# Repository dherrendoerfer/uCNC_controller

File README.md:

Copyright (C) 2014,2015,2016,2017 D.Herrendoerfer 

# uCNC_controller: A small Arduino CNC

uCNC_controller is a small CNC G-Code interpreting controller for educational or home projects.  
It supports small set of commands and can be configured to behave in several different ways.  
Included in the Extras directory are sample files to replicate a controller circuit board and  
3D files to build a small 3 axis CNC plotter.

### uCNC_controller:
It controls up to three stepper motors via the Arduino stepper library, as well as one servo, and  
two general purpose outputs. It is programmed for simplicity and readability more than for being  
a feature-complete g-code interpreter. It is intended to be a stepping stone for people intending  
to learn about machine control.

### The Extras:
Within the Extras directory there are tools, layout and schematic files, control firmwares to  
extend the basic use example of a simple plotter. Feel free to delve.

Please read the included **uCNC_controller/README.txt** file for more information.  
Please read the included **LICENSE** files and make sure you understand them before redistributing anything from this repo.

### More Information
The original source code of uCNC_controller was developed for this project in 2013  

Also, feel free to check out my [YouTube Channel](https://www.youtube.com/channel/UCe9XrOQuQR8SzbB_zRUIf0w "Dirk Herrendoerfers YouTube Channel")
all the source code and project files from the projects  
featured on the channel are hosted here.

### Ready to order PCBs for uCNC_Controller
The circuit boards for the uCNC projects are available for viewing at the EasyEDA online PCB design 
web site and can be ordered directly through JCLPCB from that site. 

The direct link to my project space on EasyEDA is [https://easyeda.com/dherrendoerfer](https://easyeda.com/dherrendoerfer "Dirk Herrendoerfers EasyEDA Projects")

## Notes
- The beta directory contains pre-release versions of the controller firmware.
- To build the uCNC_controller firmware the Arduino stepper library is required.
- The firmware requires a 5V Arduino board with at least 13 digital and 6 Analog I/O ports.  
- Recommended are 32k of flash memory.  
- Among the supported boards are: Arduino Uno, Arduino Nano, Arduino Mega 2560, and many more.
- This is work-in-progress. Check back frequently.

Donations:  
If you would like to make a donation to keep this project and others going you can do so at:  
https://www.paypal.me/dherrendoerfer  
This helps a lot !

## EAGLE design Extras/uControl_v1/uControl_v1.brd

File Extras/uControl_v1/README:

Included here is a prototype layout for a controller circuit.

The uControl board is different from the previous versions and 
requires a different firmware than the other versions.

Features are:
--------------
Support for 3 bipolar steppers using A4988 Polulu driver modules.
Support for 1 servo
Support for 8 input lines 6 bare, 2 as switch inputs
Support for 1 high load output (5A/PWM)
Support for breakout of serial and reset lines

uControl_v1.sch
----------------
  The layout schematic file

uControl_v1.brd
----------------
  The layout source file (just the layout)

uControl_v1.ps, uControl_v1.pdf
--------------------------------
  Exported layout formats of the above board

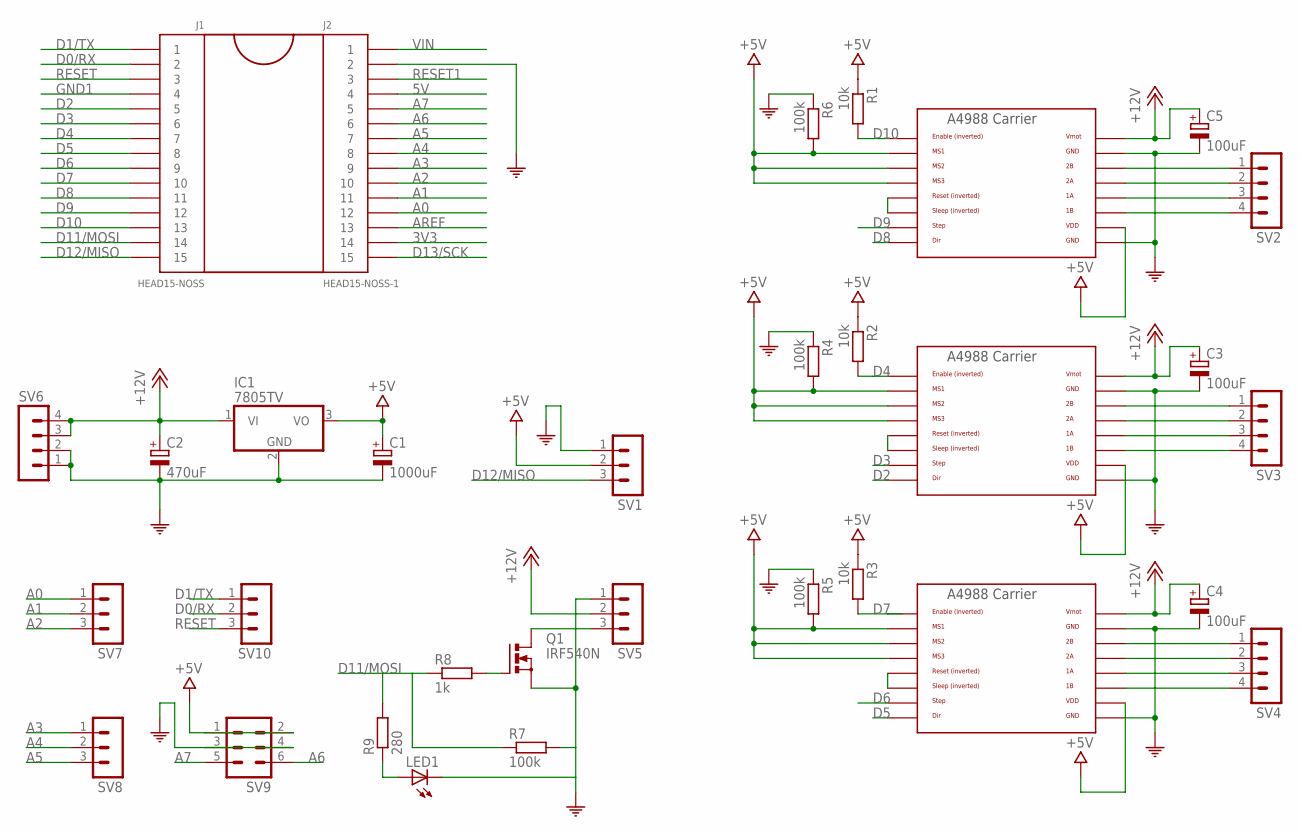
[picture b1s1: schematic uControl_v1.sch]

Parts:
C1: 1000uF; TAP5-70
C2: 470uF; TAP5-70
C3, C4, C5: 100uF; TAP5-70
IC1: 7805TV; TO220V
J1: HEAD15-NOSS
J2: HEAD15-NOSS-1
LED1: LED3MM
Q1: IRF540N; TO220BV
R1, R2, R3: 10k; 0207/10
R4, R5, R6, R7: 100k; 0207/10
R8: 1k; 0207/10
R9: 280; 0207/10
SV1, SV5, SV7, SV8, SV10: MA03-1
SV2, SV3, SV4, SV6: MA04-1
SV9: MA03-2
U$3: POLOLU_A4983CARRIER; A4988BREAKOUT
U$4, U$5: A4988BREAKOUT

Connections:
3V3: J2.14
5V: J2.4
+5V: C1.+, IC1.3 (VO), R1.1, R2.1, R3.1, R4.2, R5.2, R6.2, SV1.2, SV9.1, SV9.2, U$3.MS1, U$3.MS2, U$3.MS3, U$3.VDD, U$4.MS1, U$4.MS2, U$4.MS3, U$4.VDD, U$5.MS1, U$5.MS2, U$5.MS3, U$5.VDD
+12V: C2.+, C3.+, C4.+, C5.+, IC1.1 (VI), SV5.2, SV6.3, SV6.4, U$3.VMOT, U$4.VMOT, U$5.VMOT
A0: J2.12, SV7.1
A1: J2.11, SV7.2
A2: J2.10, SV7.3
A3: J2.9, SV8.1
A4: J2.8, SV8.2
A5: J2.7, SV8.3
A6: J2.6, SV9.6
A7: J2.5, SV9.5
AREF: J2.13
COM: C1.-, C2.-, C3.-, C4.-, C5.-, IC1.2 (GND), J2.2, LED1.K (C), Q1.S, R4.1, R5.1, R6.1, R7.2, SV1.1, SV5.1, SV6.1, SV6.2, SV9.3, SV9.4, U$3.GND, U$3.GND@0 (GND), U$4.GND, U$4.GND@0 (GND), U$5.GND, U$5.GND@0 (GND)
D0/RX: J1.2, SV10.2
D1/TX: J1.1, SV10.1
D2: J1.5, U$5.DIR
D3: J1.6, U$5.STEP
D4: J1.7, R2.2, U$5.EN
D5: J1.8, U$4.DIR
D6: J1.9, U$4.STEP
D7: J1.10, R3.2, U$4.EN
D8: J1.11, U$3.DIR
D9: J1.12, U$3.STEP
D10: J1.13, R1.2, U$3.EN
D11/MOSI: J1.14, R7.1, R8.1, R9.2
D12/MISO: J1.15, SV1.3
D13/SCK: J2.15
GND1: J1.4
unnamed: LED1.A, R9.1
unnamed: U$4.RST, U$4.SLP (SLEEP)
unnamed: SV2.1, U$3.2B
unnamed: U$3.RST, U$3.SLP (SLEEP)
unnamed: U$5.RST, U$5.SLP (SLEEP)
unnamed: SV2.2, U$3.2A
unnamed: SV2.3, U$3.1A
unnamed: SV2.4, U$3.1B
unnamed: SV3.1, U$5.2B
unnamed: SV3.2, U$5.2A
unnamed: SV3.3, U$5.1A
unnamed: SV3.4, U$5.1B
unnamed: SV4.1, U$4.2B
unnamed: SV4.2, U$4.2A
unnamed: SV4.3, U$4.1A
unnamed: SV4.4, U$4.1B
unnamed: Q1.D, SV5.3
unnamed: Q1.G, R8.2
RESET: J1.3, SV10.3
RESET1: J2.3
VIN: J2.1

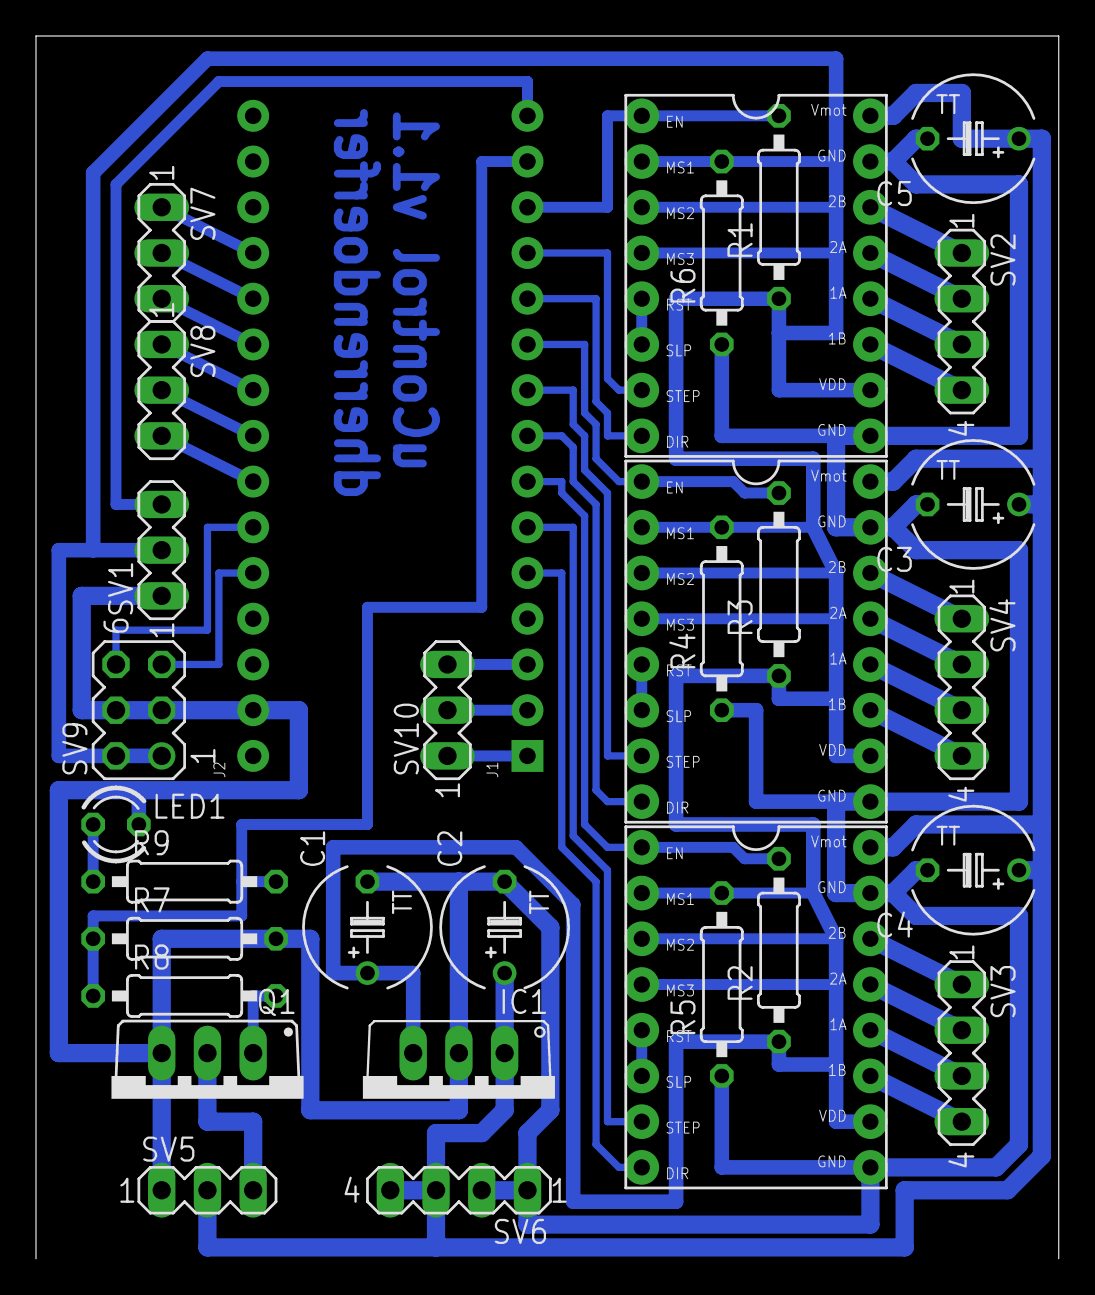
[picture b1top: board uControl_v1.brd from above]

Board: 2 copper layers, 56.8 x 67.9 mm, 32 parts (0 on the bottom side), 43 nets.

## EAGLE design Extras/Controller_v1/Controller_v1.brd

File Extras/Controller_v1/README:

Included here is a prototype layout for a controller circuit.
This controller circuit is identical to the Controller.brd 
with the exception that the Laser is driven with 12V, not 5V.

-- Beta warning: this has not jet been fully tested by me.

Controller_v1.brd
--------------
  The layout source file

Controller_v1.sch
--------------
  The schematic source file.

  Controller_v1.hpgl, Controller_v1.ps
--------------------------------------
  Exported layout formats of the above board

Controller_v1.hpgl.nc
---------------------
  A g-code sample file that will produce a plot of the above
  board using the included board and firmware.

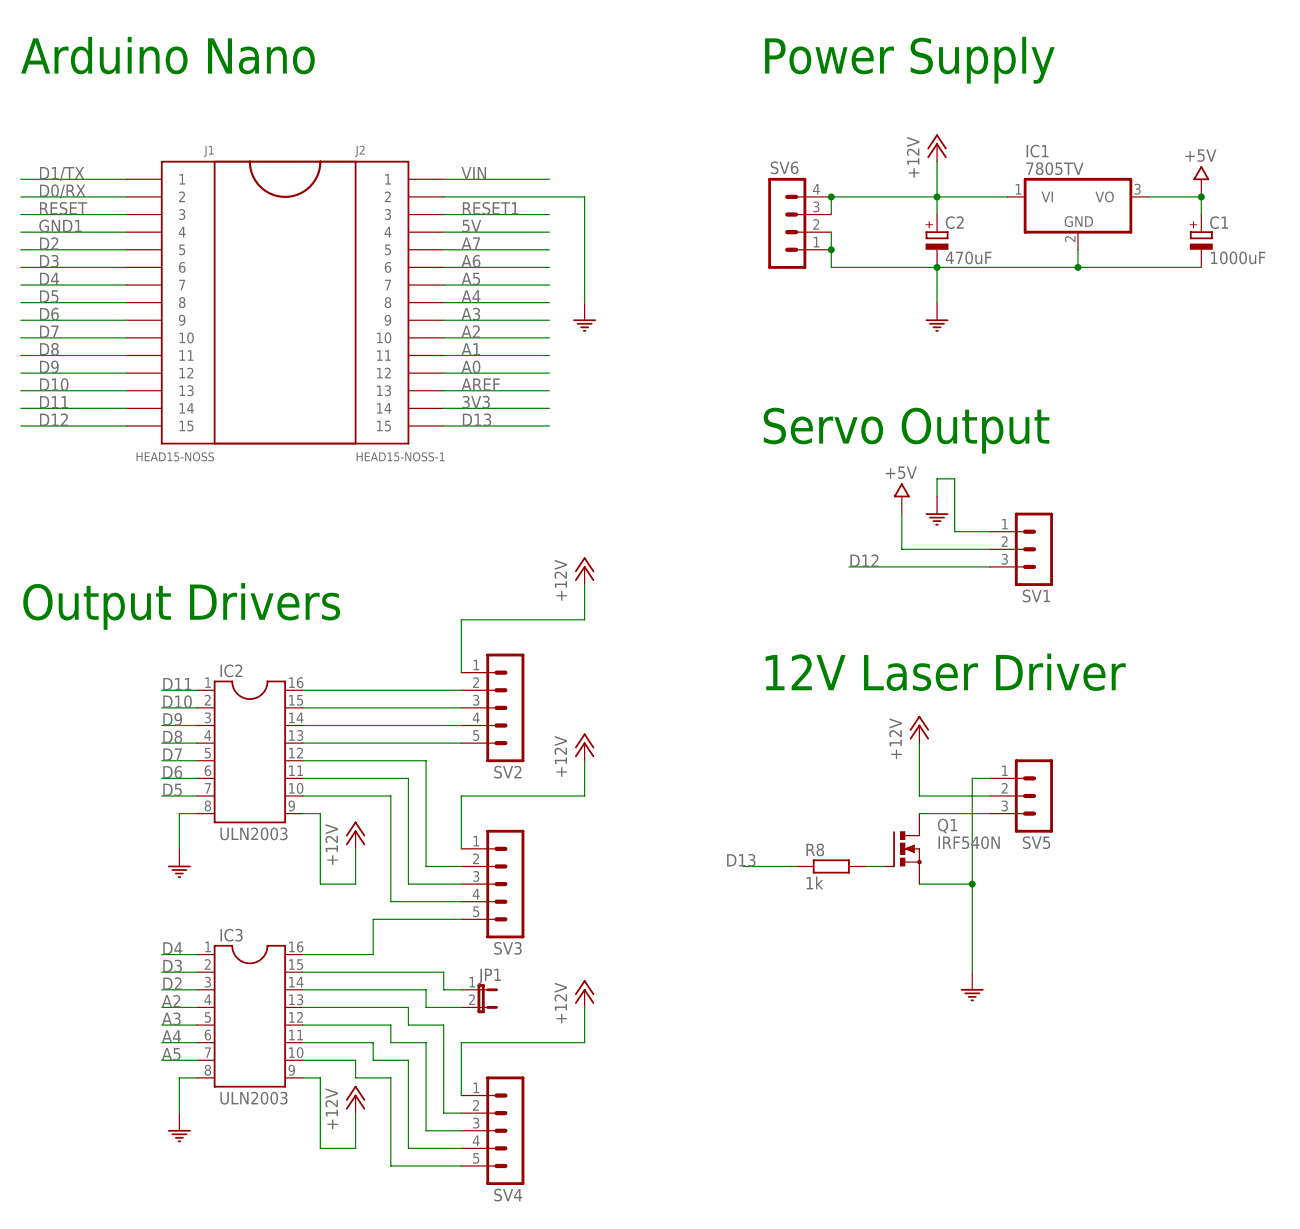
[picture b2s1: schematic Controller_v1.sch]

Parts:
C1: 1000uF; TAP5-70
C2: 470uF; TAP5-70
IC1: 7805TV; TO220V
IC2, IC3: ULN2003; DIL16
J1: HEAD15-NOSS
J2: HEAD15-NOSS-1
JP1: JP1E; JP1
Q1: IRF540N; TO220BV
R8: 1k; 0207/10
SV1, SV5: MA03-1
SV2, SV3, SV4: MA05-1
SV6: MA04-1

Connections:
3V3: J2.14
5V: J2.4
+5V: C1.+, IC1.3 (VO), SV1.2
+12V: C2.+, IC1.1 (VI), IC2.9, IC3.9, SV2.1, SV3.1, SV4.1, SV5.2, SV6.3, SV6.4
A0: J2.12
A1: J2.11
A2: IC3.4, J2.10
A3: IC3.5, J2.9
A4: IC3.6, J2.8
A5: IC3.7, J2.7
A6: J2.6
A7: J2.5
AREF: J2.13
COM: C1.-, C2.-, IC1.2 (GND), IC2.8, IC3.8, J2.2, Q1.S, SV1.1, SV5.1, SV6.1, SV6.2
D0/RX: J1.2
D1/TX: J1.1
D2: IC3.3, J1.5
D3: IC3.2, J1.6
D4: IC3.1, J1.7
D5: IC2.7, J1.8
D6: IC2.6, J1.9
D7: IC2.5, J1.10
D8: IC2.4, J1.11
D9: IC2.3, J1.12
D10: IC2.2, J1.13
D11: IC2.1, J1.14
D12: J1.15, SV1.3
D13: J2.15, R8.1
GND1: J1.4
unnamed: IC3.15, JP1.1
unnamed: IC3.14, JP1.2
unnamed: IC3.13, SV4.2
unnamed: IC3.12, SV4.3
unnamed: IC3.16, SV3.5
unnamed: IC3.11, SV4.4
unnamed: IC3.10, SV4.5
unnamed: Q1.D, SV5.3
unnamed: Q1.G, R8.2
unnamed: IC2.16, SV2.2
unnamed: IC2.15, SV2.3
unnamed: IC2.14, SV2.4
unnamed: IC2.13, SV2.5
unnamed: IC2.12, SV3.2
unnamed: IC2.11, SV3.3
unnamed: IC2.10, SV3.4
RESET: J1.3
RESET1: J2.3
VIN: J2.1

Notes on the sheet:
Arduino Nano
Output Drivers
Power Supply
Servo Output
12V Laser Driver

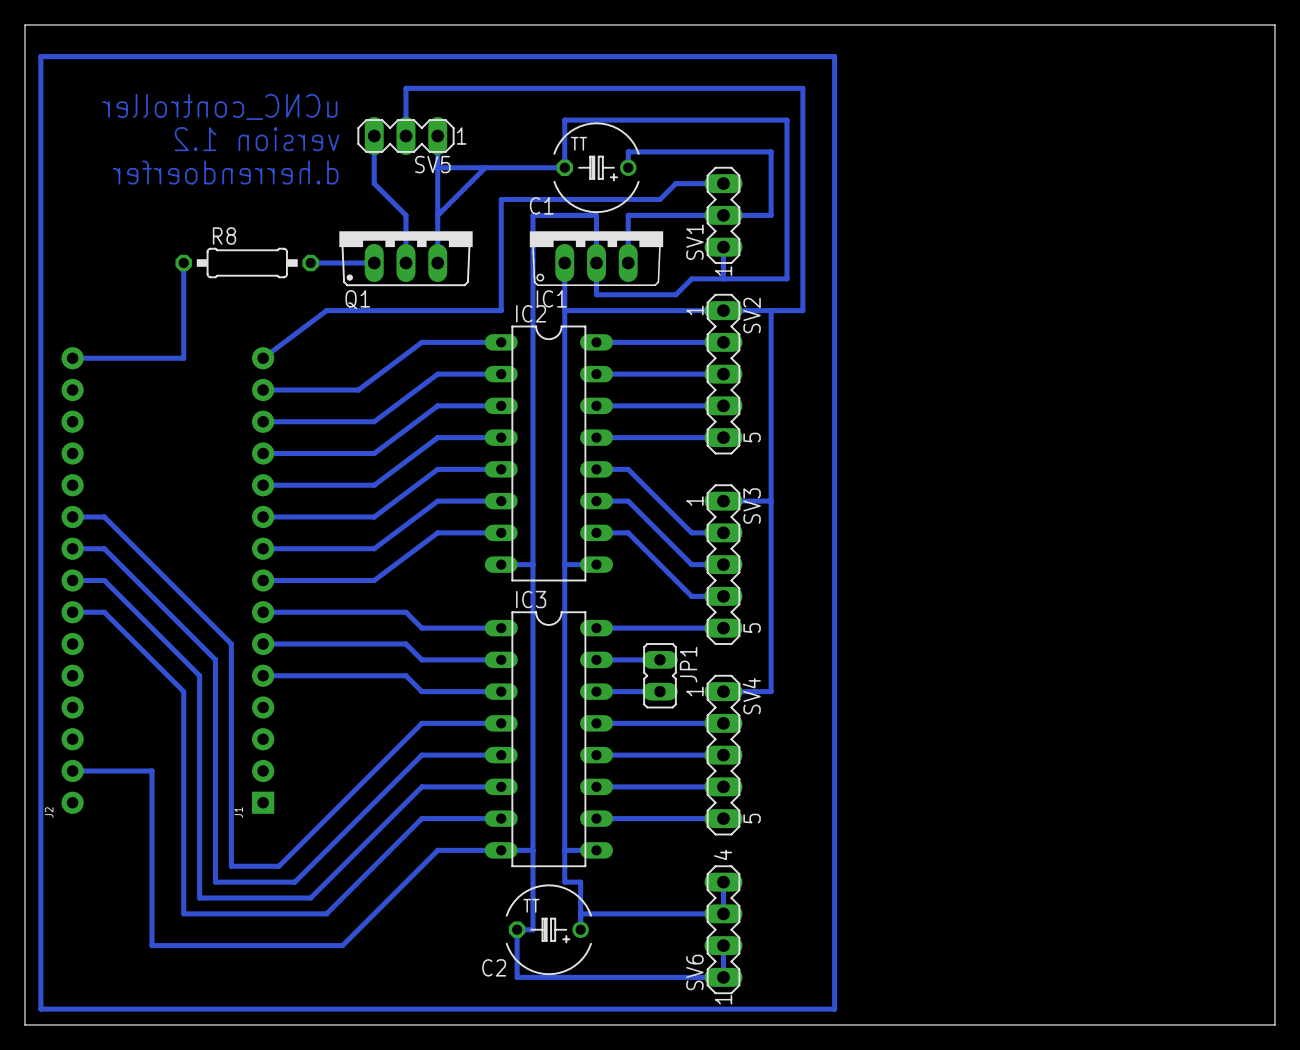
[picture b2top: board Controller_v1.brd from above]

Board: 2 copper layers, 100.0 x 80.0 mm, 16 parts (0 on the bottom side), 35 nets.

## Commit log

2014-02-09 Initial check-in.
2014-02-10 Updated documentation
2014-02-11 More documentation
2014-04-24 This commit adds the files needed to produce a small plotter that will work with this firmware. Included is the layout of a controller board and 3D files to print the required parts for the plotter i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
2014-04-24 Updated README file.
2014-07-14 Fix erroreous stepper speed setting in mode 1
2014-07-15 Add beta code for version 2
2014-07-15 Update beta version nummer
2014-07-17 Update beta readme file
2014-08-01 Update the stl files for the plotter to better work with slic3r.
2014-08-26 Update B.O.M.
2014-08-26 Update README file
2014-09-30 Add the files for the version 4 plotter, firmware, and controller.
2014-10-03 Add v4 beta code and reorganize directory structure
2014-10-07 Clean up to merge v1 and v4 controller codebase.
2014-11-18 Fix initializarion and position reset
2014-12-03 Organize the file and directory structure so sketches are easier to directly open in Arduino IDE if the git has been downloaded as a zip file (hopefully)
2014-12-28 Add schematic and board for the reworked v1 controller board.
2014-12-29 Add missing Controller_v1 files
2015-01-04 Add an ID string to the boot message
2015-01-08 Add GcodeWriter
2015-05-11 Fixed an initialization bug.
2015-05-27 Add Hp2xx Windows console application
2015-07-07 Added GRBL Polulu shield output layout
2015-07-08 Updates for GRBL-Shield support
2015-07-08 Add some cleanup and changes for the GRBL Shield. Also fix some minor issues with Z-Axis handling
2016-04-18 Fixed a nasty bug that would hit if the build area was bigger than 32k native steps.
2016-04-18 Fixed the same nasty 32k steps bug in the beta of the v1 firmware
2016-04-21 Fixed some typos, added more structure to the documentation, added copyright assignments to non-source files, as some forks and clones of this software have appeared that have the copyright assignmen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
2016-09-13 Update README for readability.
2016-09-14 Add new v6 beta code.
2016-12-27 Add v3 AllParts stl file
2016-12-31 Add v4 plotter files
2017-01-09 Update to documentation
2017-01-09 Documentation updates
2017-01-11 Circumvent timing issue
2017-01-11 Fix servo init timing issue
2017-01-12 Work to revive auto homing
2017-01-13 Back to conservative defaults for homing
2017-01-16 Small updates and license date changes, wip
2017-01-17 Push v6 beta to newest version, adding alpha servo support
2017-01-27 Introducing the engraver mode
2017-01-29 Add first beta of gcode4bmps.py
2017-02-01 Update readme, add test tux file.
2017-02-15 Add first set of parts to Rod-Robin CNC build
2017-03-15 Added documentation into the output file and raised pdf output dpi to 600
2017-05-25 Adding new code from recent projects
2017-08-25 Clean up documentation and fix a small issue in gcode4bmps
2017-08-25 Fix error in Z depth setting
2017-09-05 Add new functions for DPI handling and a cutout helper
2017-09-23 Add simple engraver support with spindle-on/off semantics
2017-10-09 Introduce V1_COMPACT board definition
2017-11-02 Add the LED-HMD code
2017-11-23 Updated docu to include links to EasyEDA.
2017-11-23 Fix conflicts
2017-12-22 Slight rework to make board definitions more apparent.
2017-12-22 Also add the other board definition files
2018-01-10 Add STL files for each single part of Plotter_v4
2018-01-29 Changed tkinter imports for python 3
2018-05-26 Typo fixes
    Fixed typos in the word application and the word millimeter.
